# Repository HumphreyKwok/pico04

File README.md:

# pico04
A Cherry MX 4-key pad for fun. </br>
Cosidering the size limitation, Atemage16u2MU is used instead of 32u4AU. </br>

## Features
- USB Type-C connector
- ESD protection
- Support per-switch RGB backlight
- Hotswappable
- Support QMK firmware

## Upcoming featues
- Bottom mount PCB case
- Support VIA

## Acknowledgements
Basically I designed this board on ai03's tutorial, step by step. This PCB won't even exist without the help of ai03's previous works and foorprint libraies.
On the other hand, coseyfannitutti and Hadi Iskandarani also advise me a lot during the development of this project. </br>

ai03's wiki and PCB : https://wiki.ai03.me/books/pcb-design </br>

coseyfannitutti's github : https://github.com/coseyfannitutti </br>

Hadi's Youtube Channel and machanical keyboard design tutorials : https://youtu.be/BhFqkVggv8Q </br>

Thanks all.

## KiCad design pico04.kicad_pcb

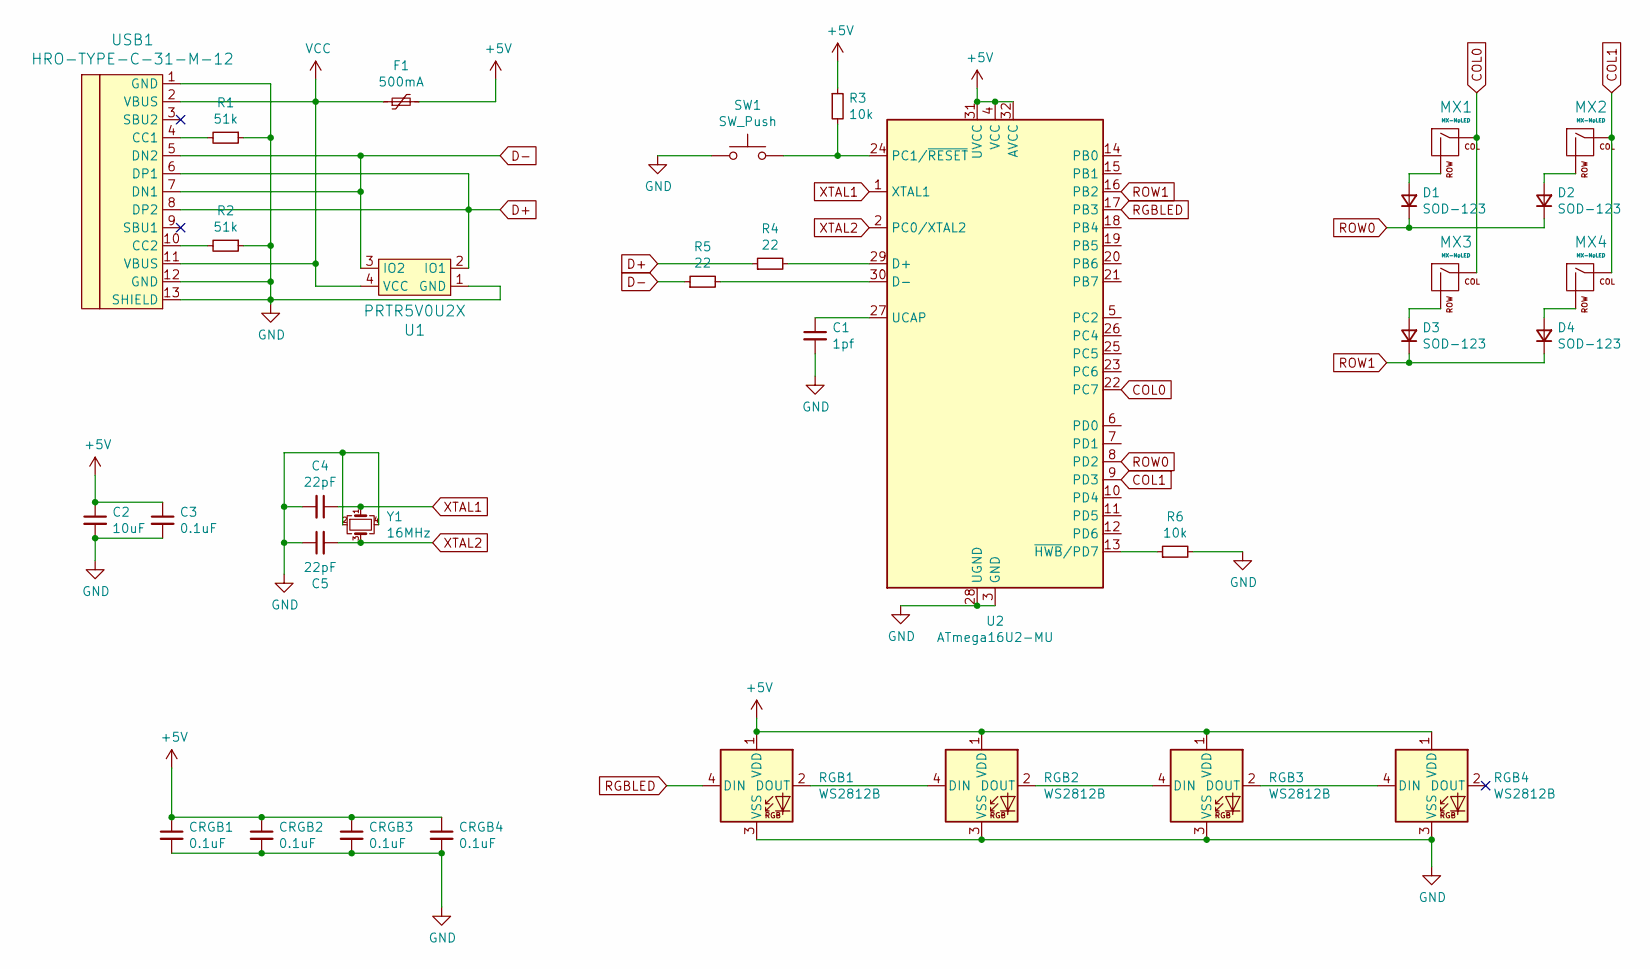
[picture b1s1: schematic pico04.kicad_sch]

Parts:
C1: 1pf; C_0805_2012Metric
C2: 10uF; C_0805_2012Metric
C3: 0.1uF; C_0805_2012Metric
C4, C5: 22pF; C_0805_2012Metric
CRGB1, CRGB2, CRGB3, CRGB4: 0.1uF; C_0603_1608Metric
D1, D2, D3, D4: SOD-123; D_SOD-123
F1: 500mA; Fuse_1206_3216Metric
MX1, MX2, MX3, MX4: MX-NoLED; MXOnly-1U-Hotswap
R1, R2: 51k; R_0805_2012Metric
R3, R6: 10k; R_0805_2012Metric
R4, R5: 22; R_0805_2012Metric
RGB1, RGB2, RGB3, RGB4: WS2812B; WS2812B-3528
SW1: SW_Push; SKQGADE010
U1: PRTR5V0U2X; SOT143B
U2: ATmega16U2-MU; QFN-32-1EP_5x5mm_P0.5mm_EP3.1x3.1mm
USB1: HRO-TYPE-C-31-M-12
Y1: 16MHz; Crystal_SMD_3225-4Pin_3.2x2.5mm

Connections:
+5V: C2.1, C3.1, CRGB1.1, CRGB2.1, CRGB3.1, CRGB4.1, F1.2, R3.1, RGB1.1 (VDD), RGB2.1 (VDD), RGB3.1 (VDD), RGB4.1 (VDD), U2.4 (VCC), U2.31 (UVCC), U2.32 (AVCC)
COL0: MX1.1 (COL), MX3.1 (COL), U2.22 (PC7)
COL1: MX2.1 (COL), MX4.1 (COL), U2.9 (PD3)
D+: R4.1, U1.2 (IO1), USB1.6 (DP1), USB1.8 (DP2)
D-: R5.1, U1.3 (IO2), USB1.5 (DN2), USB1.7 (DN1)
GND: C1.2, C2.2, C3.2, C4.2, C5.1, CRGB1.2, CRGB2.2, CRGB3.2, CRGB4.2, R1.1, R2.1, R6.2, RGB1.3 (VSS), RGB2.3 (VSS), RGB3.3 (VSS), RGB4.3 (VSS), SW1.1, U1.1 (GND), U2.3 (GND), U2.28 (UGND), U2.33 (GND), USB1.1 (GND), USB1.12 (GND), USB1.13 (SHIELD), Y1.2, Y1.4
unnamed: C1.1, U2.27 (UCAP)
unnamed: D1.2 (A), MX1.2 (ROW)
unnamed: D2.2 (A), MX2.2 (ROW)
unnamed: D3.2 (A), MX3.2 (ROW)
unnamed: D4.2 (A), MX4.2 (ROW)
unnamed: R1.2, USB1.4 (CC1)
unnamed: R2.2, USB1.10 (CC2)
unnamed: R3.2, SW1.2, U2.24 (PC1/~RESET)
unnamed: R4.2, U2.29 (D+)
unnamed: R5.2, U2.30 (D-)
unnamed: R6.1, U2.13 (~HWB~/PD7)
unnamed: RGB1.2 (DOUT), RGB2.4 (DIN)
unnamed: RGB2.2 (DOUT), RGB3.4 (DIN)
unnamed: RGB3.2 (DOUT), RGB4.4 (DIN)
RGBLED: RGB1.4 (DIN), U2.17 (PB3)
ROW0: D1.1 (K), D2.1 (K), U2.8 (PD2)
ROW1: D3.1 (K), D4.1 (K), U2.16 (PB2)
VCC: F1.1, U1.4 (VCC), USB1.2 (VBUS), USB1.11 (VBUS)
XTAL1: C4.1, U2.1 (XTAL1), Y1.1
XTAL2: C5.2, U2.2 (PC0/XTAL2), Y1.3

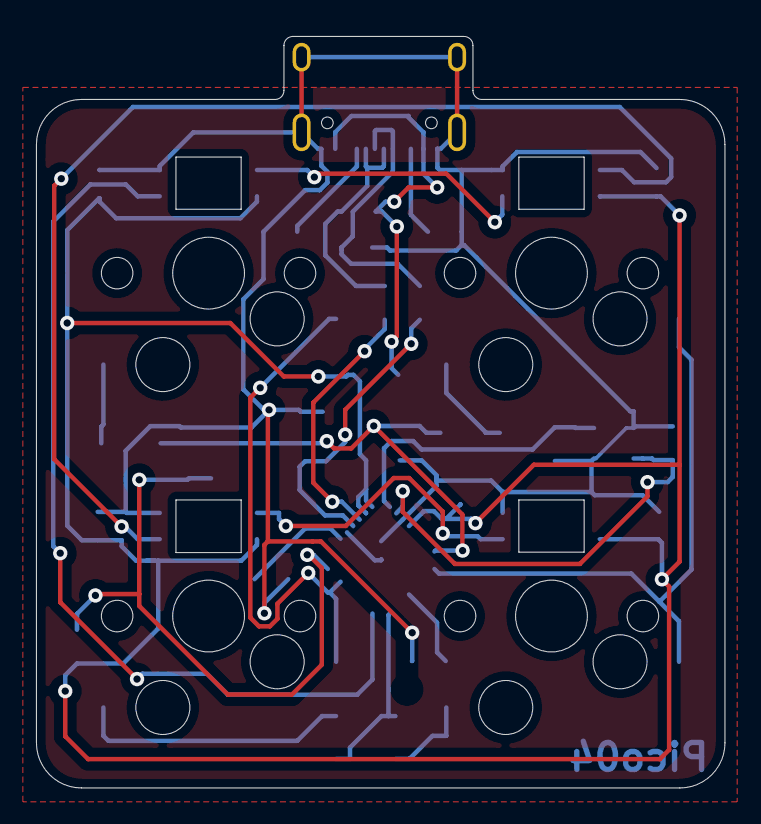
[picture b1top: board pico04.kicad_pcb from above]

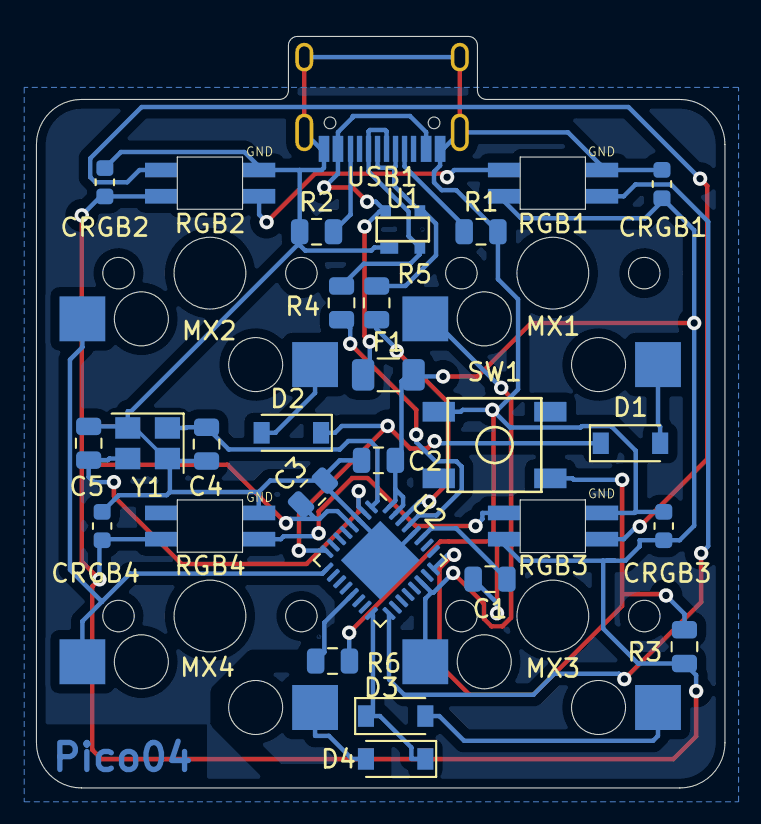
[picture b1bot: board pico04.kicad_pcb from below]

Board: 2 copper layers, 38.2 x 41.8 mm, 33 parts (29 on the bottom side), 26 nets.

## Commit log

2020-06-21 Add footprint libraries
2020-06-21 Complete the schematic
2020-06-21 Created a ws2812-3528 footprint
2020-06-21 Place the footprint on the PCB
2020-06-22 Complete the PCB
2020-06-22 Add some 3d models to the PCB
2020-06-22 Fix 3d model issues
2020-06-22 Add 3d images of the PCB
2020-06-22 Re-route the PCB
2020-06-22 Optimize some routing and update the images
2020-08-28 Test

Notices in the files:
pico04.kicad_sch:
License: MIT
